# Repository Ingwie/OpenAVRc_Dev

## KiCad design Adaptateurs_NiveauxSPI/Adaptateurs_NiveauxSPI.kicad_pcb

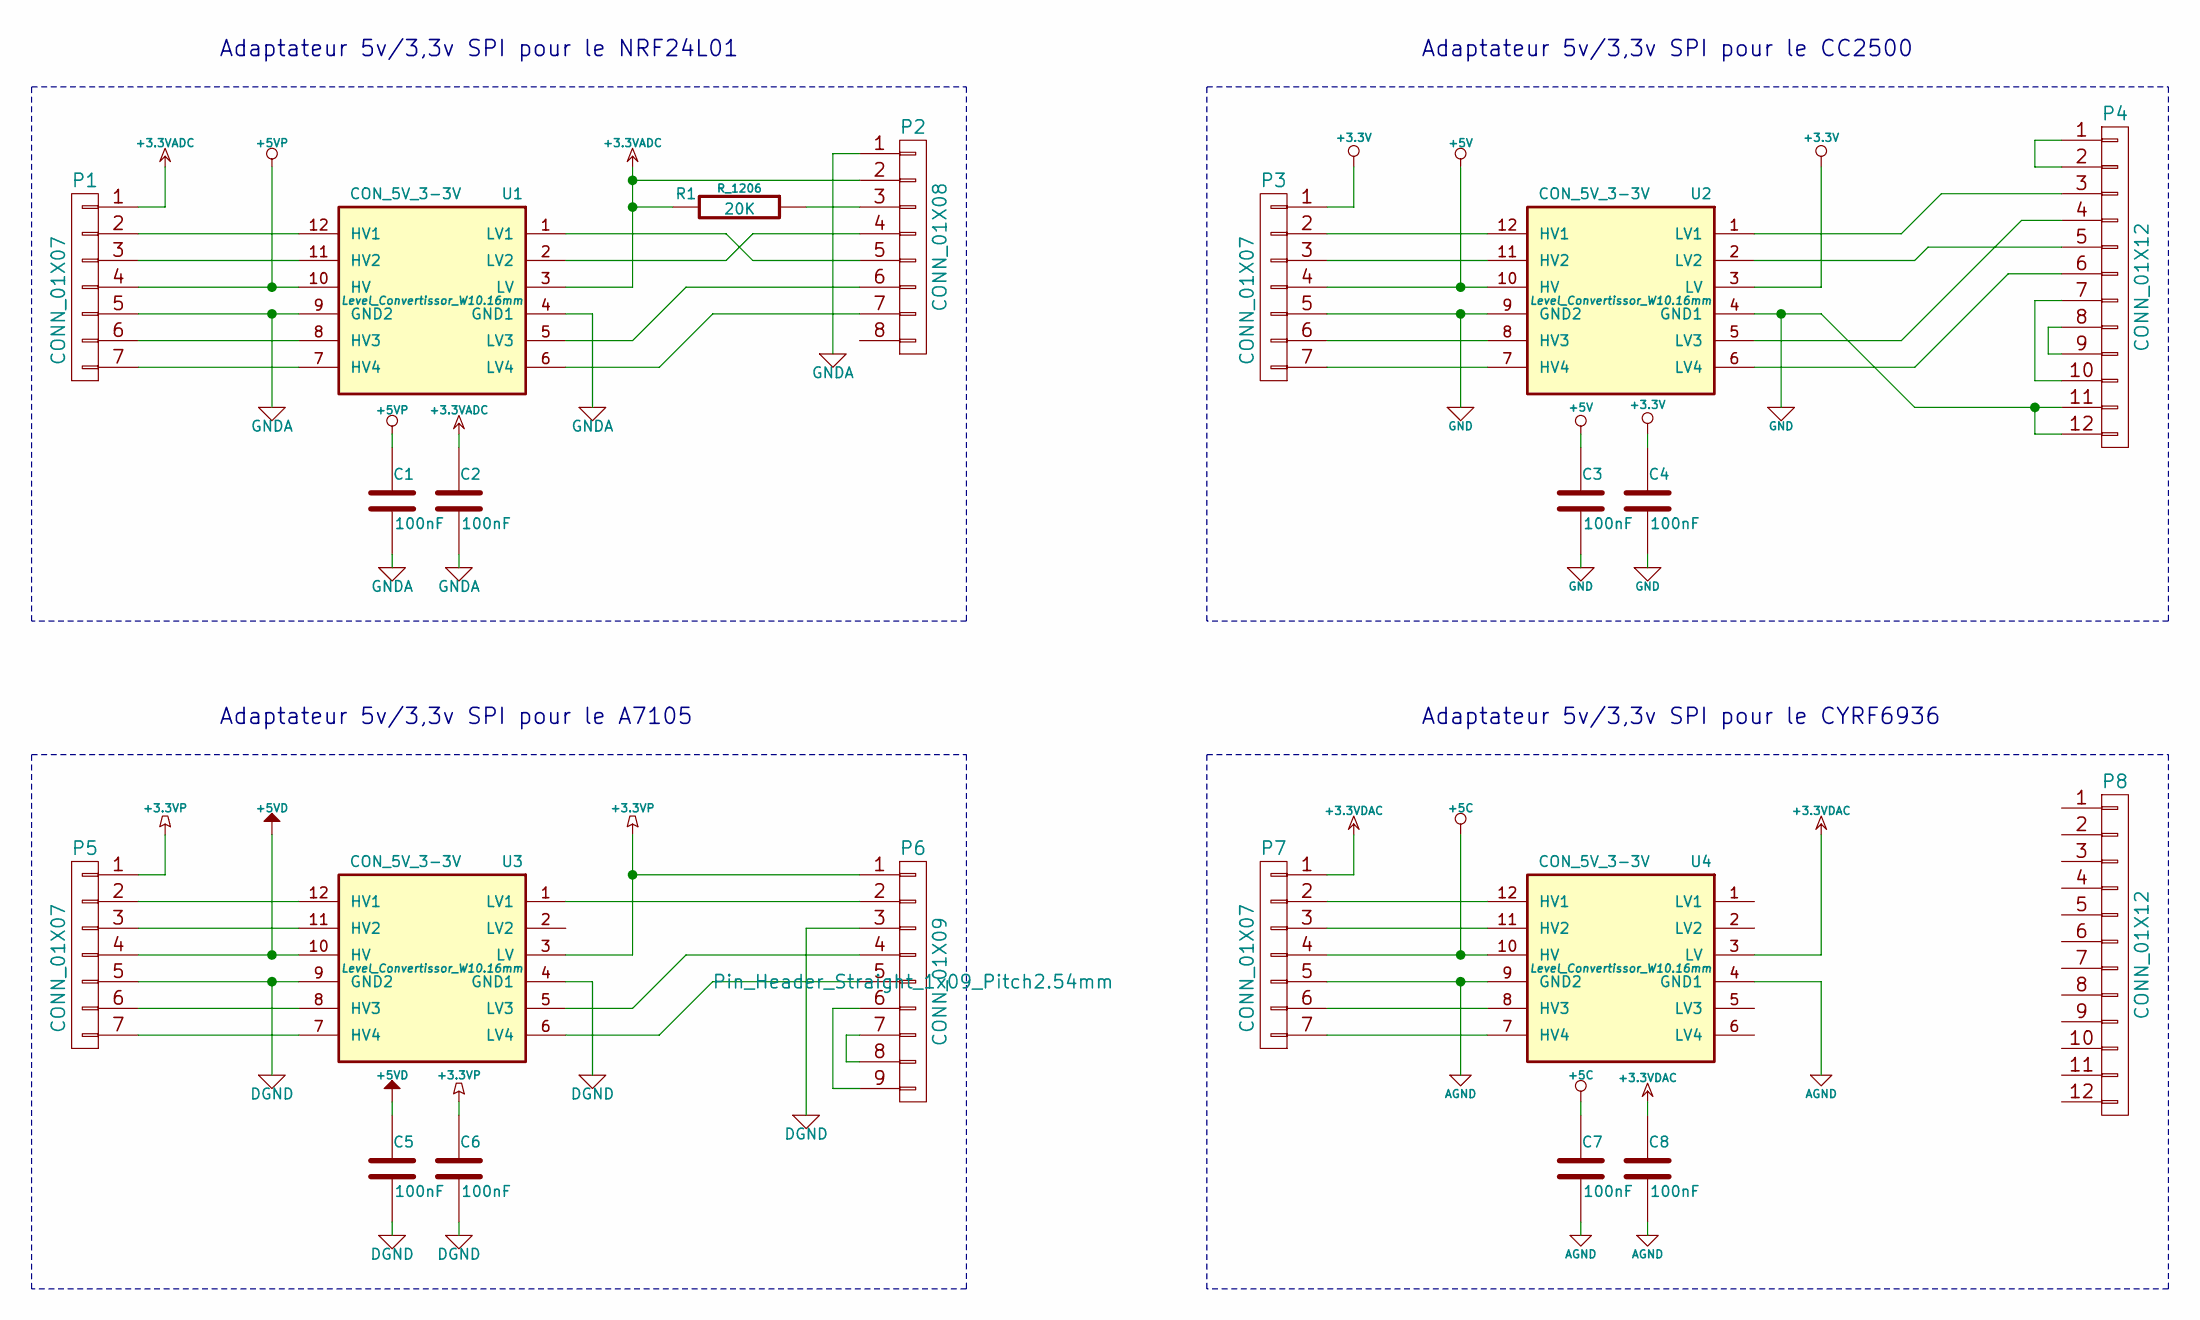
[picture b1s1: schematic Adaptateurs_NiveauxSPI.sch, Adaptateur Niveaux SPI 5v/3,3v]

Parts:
C1, C2, C3, C4, C5, C6, C7, C8: 100nF; C_1206
P1, P3, P5, P7: CONN_01X07; Pin_Header_Straight_1x07_Pitch2.54mm
P2: CONN_01X08; Pin_Header_Straight_2x04_Pitch2.54mm
P4, P8: CONN_01X12; Pin_Header_Straight_2x06_Pitch2.54mm
P6: CONN_01X09; Pin_Header_Straight_1x09_Pitch2.54mm
R1: 20K; R_1206
U1, U2, U3, U4: CON_5V_3-3V; Level_Convertissor_W10.16mm

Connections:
+3.3V: C4.1, P3.1, U2.3 (LV)
+3.3VADC: C2.1, P1.1, P2.2, R1.2, U1.3 (LV)
+3.3VDAC: C8.1, P7.1, U4.3 (LV)
+3.3VP: C6.1, P5.1, P6.1, U3.3 (LV)
+5C: C7.1, P7.4, P8.1, U4.10 (HV)
+5V: C3.1, P3.4, U2.10 (HV)
+5VD: C5.1, P5.4, U3.10 (HV)
+5VP: C1.1, P1.4, U1.10 (HV)
AGND: C7.2, C8.2, P7.5, P8.6, U4.4 (GND1), U4.9 (GND2)
DGND: C5.2, C6.2, P5.5, P6.3, U3.4 (GND1), U3.9 (GND2)
GND: C3.2, C4.2, P3.5, P4.11, P4.12, U2.4 (GND1), U2.9 (GND2)
GNDA: C1.2, C2.2, P1.5, P2.1, U1.4 (GND1), U1.9 (GND2)
unnamed: P1.2, U1.12 (HV1)
unnamed: P1.3, U1.11 (HV2)
unnamed: P1.6, U1.8 (HV3)
unnamed: P1.7, U1.7 (HV4)
unnamed: P2.3, R1.1
unnamed: P2.4, U1.2 (LV2)
unnamed: P2.5, U1.1 (LV1)
unnamed: P2.6, U1.5 (LV3)
unnamed: P2.7, U1.6 (LV4)
unnamed: P3.2, U2.12 (HV1)
unnamed: P3.3, U2.11 (HV2)
unnamed: P3.6, U2.8 (HV3)
unnamed: P3.7, U2.7 (HV4)
unnamed: P4.1, P4.2
unnamed: P4.3, U2.1 (LV1)
unnamed: P4.4, U2.5 (LV3)
unnamed: P4.5, U2.2 (LV2)
unnamed: P4.6, U2.6 (LV4)
unnamed: P4.8, P4.9
unnamed: P4.7, P4.10
unnamed: P5.2, U3.12 (HV1)
unnamed: P5.3, U3.11 (HV2)
unnamed: P5.6, U3.8 (HV3)
unnamed: P5.7, U3.7 (HV4)
unnamed: P6.2, U3.1 (LV1)
unnamed: P6.4, U3.5 (LV3)
unnamed: P6.5, U3.6 (LV4)
unnamed: P6.6, P6.9
unnamed: P6.7, P6.8
unnamed: P7.2, U4.12 (HV1)
unnamed: P7.3, U4.11 (HV2)
unnamed: P7.6, U4.8 (HV3)
unnamed: P7.7, U4.7 (HV4)
unnamed: P8.2, U4.1 (LV1)
unnamed: P8.4, U4.2 (LV2)
unnamed: P8.8, U4.5 (LV3)
unnamed: P8.10, U4.6 (LV4)

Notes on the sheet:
Adaptateur 5v/3,3v SPI pour le NRF24L01
Adaptateur 5v/3,3v SPI pour le CC2500
Adaptateur 5v/3,3v SPI pour le A7105
Adaptateur 5v/3,3v SPI pour le CYRF6936

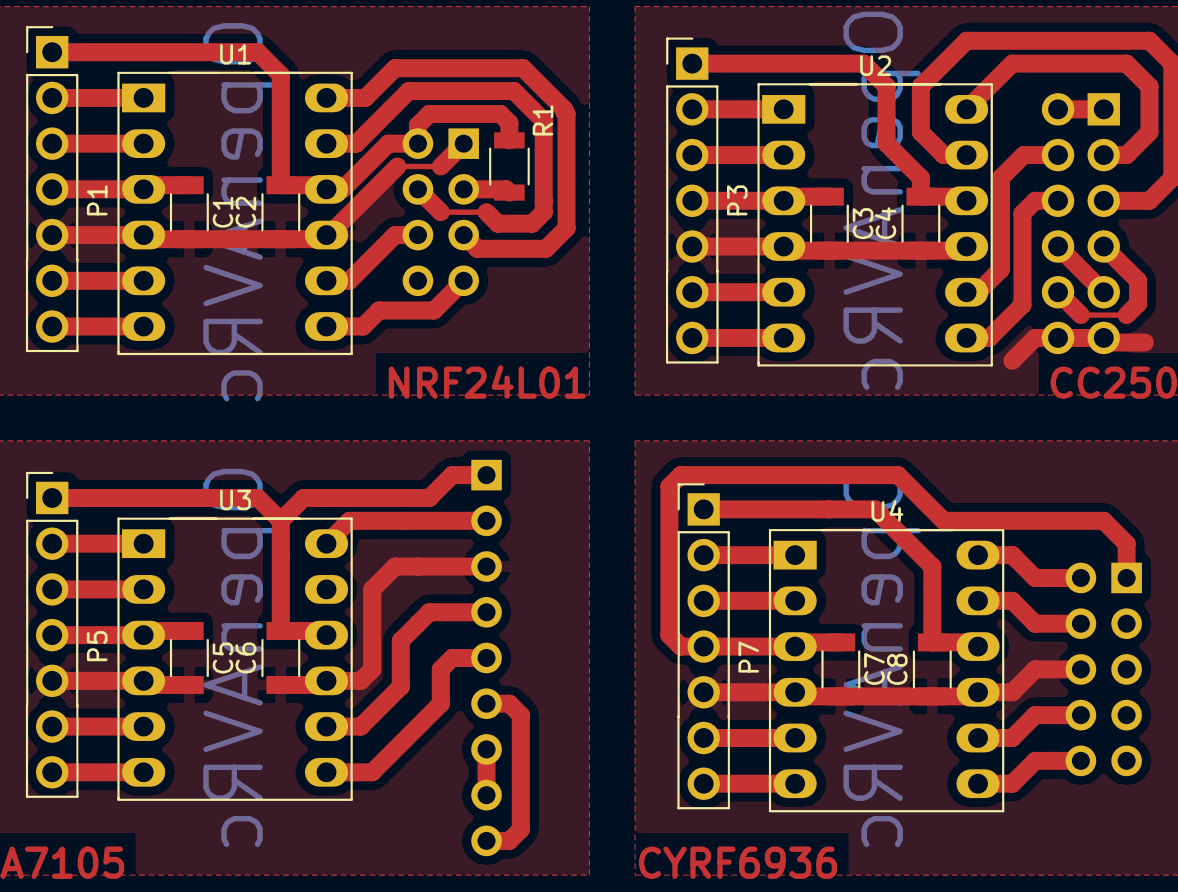
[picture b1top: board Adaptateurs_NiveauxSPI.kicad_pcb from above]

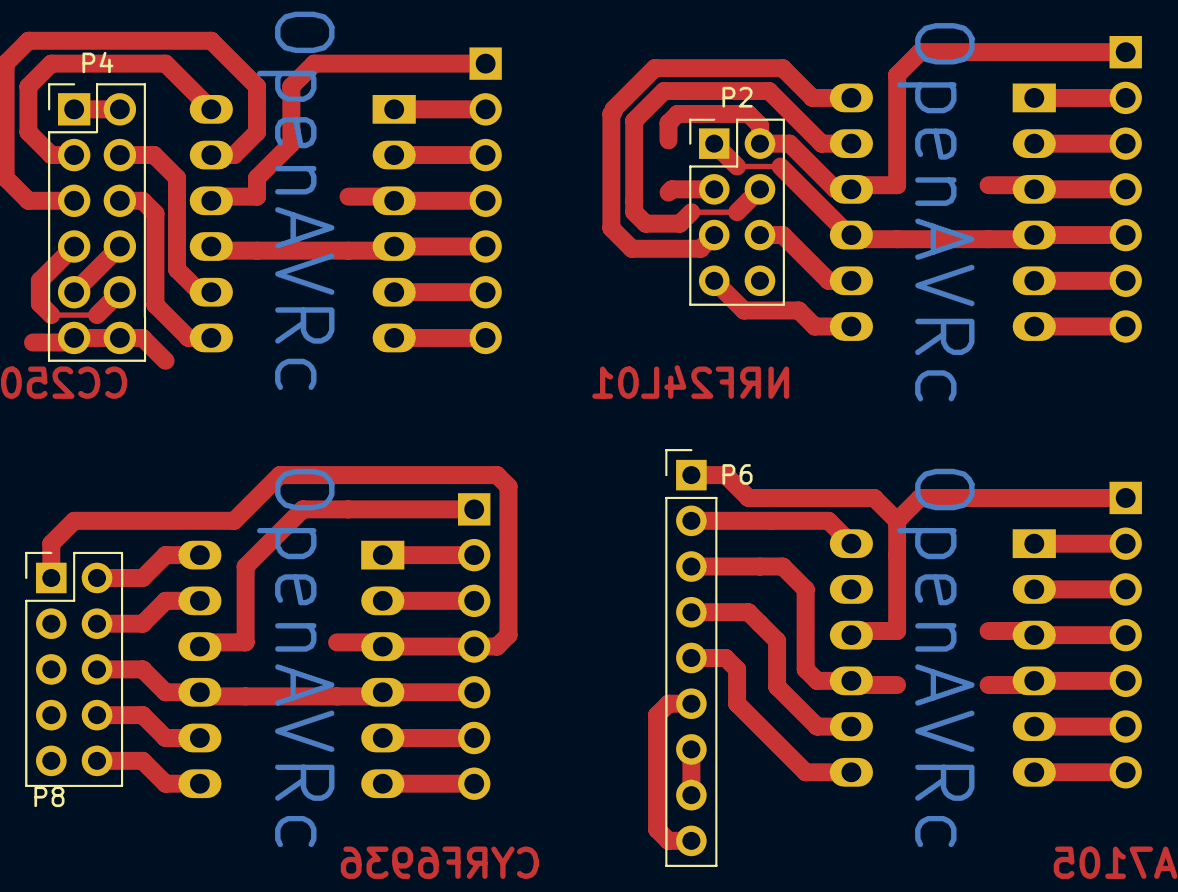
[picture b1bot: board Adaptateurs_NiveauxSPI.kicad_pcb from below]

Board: 2 copper layers, 21 parts (4 on the bottom side), 49 nets.

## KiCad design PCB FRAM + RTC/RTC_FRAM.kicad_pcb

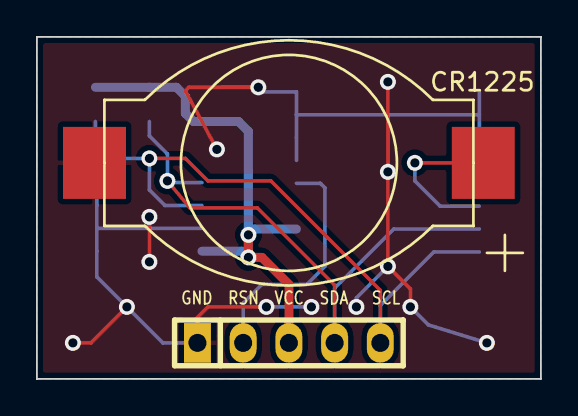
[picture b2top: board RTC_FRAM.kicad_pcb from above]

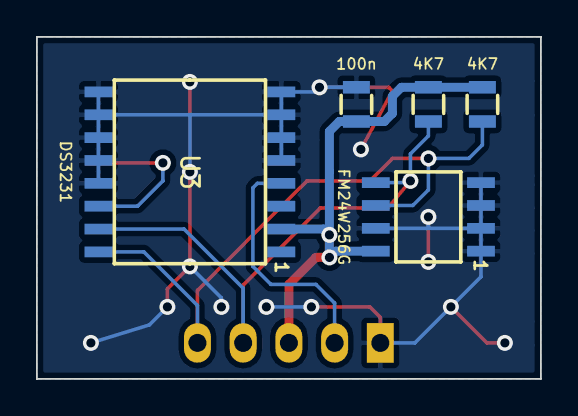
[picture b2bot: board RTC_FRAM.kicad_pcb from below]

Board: 2 copper layers, 28.0 x 19.0 mm, 7 parts (5 on the bottom side), 6 nets.

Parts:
BT1: CR1225; Renata_SMTU1225-LF
C1: 100n; SM0805
J1: CONN_01X05; pin_strip_5
R1, R2: 4K7; SM0805
U2: FM24W256G; SO-8
U3: DS3231; SO-16-W

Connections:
+3V3: C1.1, J1.3, R1.1, R2.1, U2.8, U3.2
GND: BT1.2, C1.2, J1.1, U2.1, U2.2, U2.3, U2.4, U2.7, U3.5, U3.6, U3.7, U3.8, U3.9, U3.10, U3.11, U3.12, U3.13
unnamed: BT1.1, U3.14
RESET_N: J1.2, U3.4
SCL-FRAM-RTC: J1.5, R1.2, U2.6, U3.16
SDA-FRAM-RTC: J1.4, R2.2, U2.5, U3.15

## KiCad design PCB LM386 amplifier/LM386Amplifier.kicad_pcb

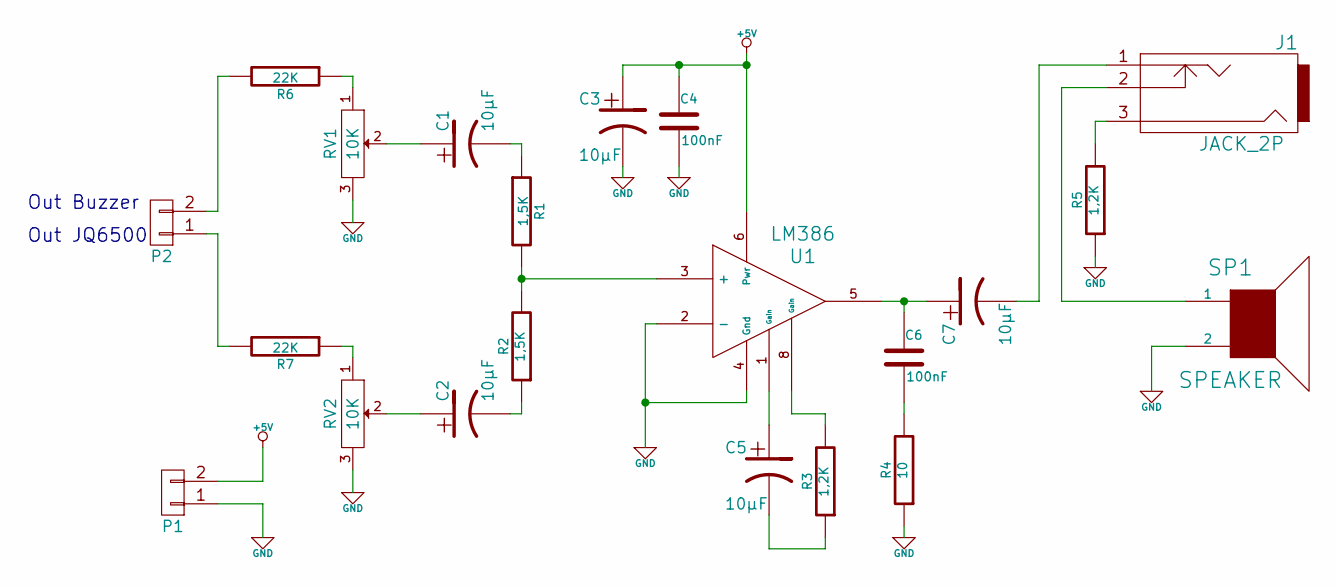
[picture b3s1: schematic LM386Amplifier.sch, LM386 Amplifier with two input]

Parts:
C1, C2, C3: 10µF; CP_Radial_D6.3mm_P2.50mm
C4, C6: 100nF; C_Rect_L7.0mm_W2.0mm_P5.00mm
C5, C7: 10µF; CP_Radial_Tantal_D6.0mm_P2.50mm
J1: JACK_2P; Pin_Header_Straight_1x03_Pitch2.54mm
P1, P2: CONN_01X02; Pin_Header_Straight_1x02_Pitch2.54mm
R1, R2: 1,5K; R_Axial_DIN0204_L3.6mm_D1.6mm_P2.54mm_Vertical
R3, R5: 1,2K; R_Axial_DIN0204_L3.6mm_D1.6mm_P2.54mm_Vertical
R4: 10; R_Axial_DIN0204_L3.6mm_D1.6mm_P2.54mm_Vertical
R6, R7: 22K; R_Axial_DIN0204_L3.6mm_D1.6mm_P2.54mm_Vertical
RV1, RV2: 10K; Potentiometer_Trimmer_Bourns_3296W.kicad_mod
SP1: SPEAKER; Pin_Header_Straight_1x02_Pitch2.54mm
U1: LM386; DIP-8_W7.62mm_LongPads

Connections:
+5V: C3.1, C4.1, P1.2, U1.6 (Pwr)
GND: C3.2, C4.2, P1.1, R4.1, R5.1, RV1.3, RV2.3, SP1.2, U1.2 (-), U1.4 (Gnd)
unnamed: C1.1, RV1.2
unnamed: C1.2, R1.1
unnamed: C2.1, RV2.2
unnamed: C2.2, R2.1
unnamed: C5.1, U1.1 (Gain)
unnamed: C5.2, R3.1
unnamed: C6.1, C7.1, U1.5
unnamed: C6.2, R4.2
unnamed: C7.2, J1.1
unnamed: J1.2, SP1.1
unnamed: J1.3, R5.2
unnamed: P2.1, R7.2
unnamed: P2.2, R6.2
unnamed: R1.2, R2.2, U1.3 (+)
unnamed: R3.2, U1.8 (Gain)
unnamed: R6.1, RV1.1
unnamed: R7.1, RV2.1

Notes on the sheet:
Out Buzzer
Out JQ6500

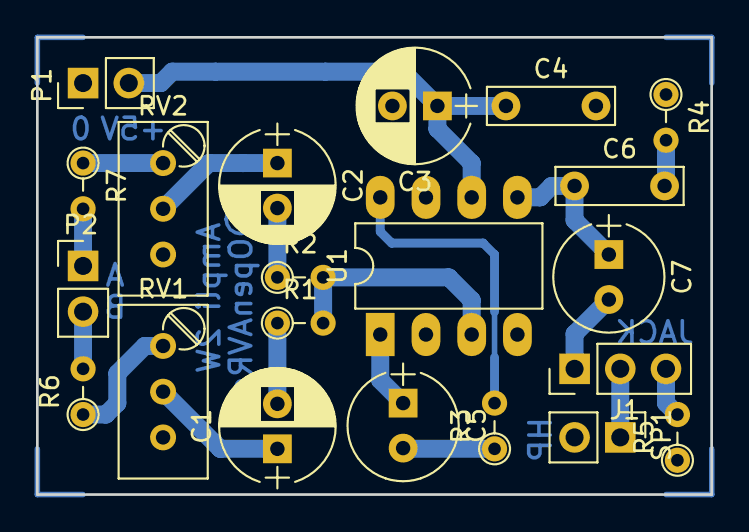
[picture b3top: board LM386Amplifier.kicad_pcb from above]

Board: 2 copper layers, 37.5 x 25.4 mm, 21 parts (0 on the bottom side), 19 nets.

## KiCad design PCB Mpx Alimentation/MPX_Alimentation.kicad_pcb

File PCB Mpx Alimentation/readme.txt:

create PCB Mpx Alimentation directory

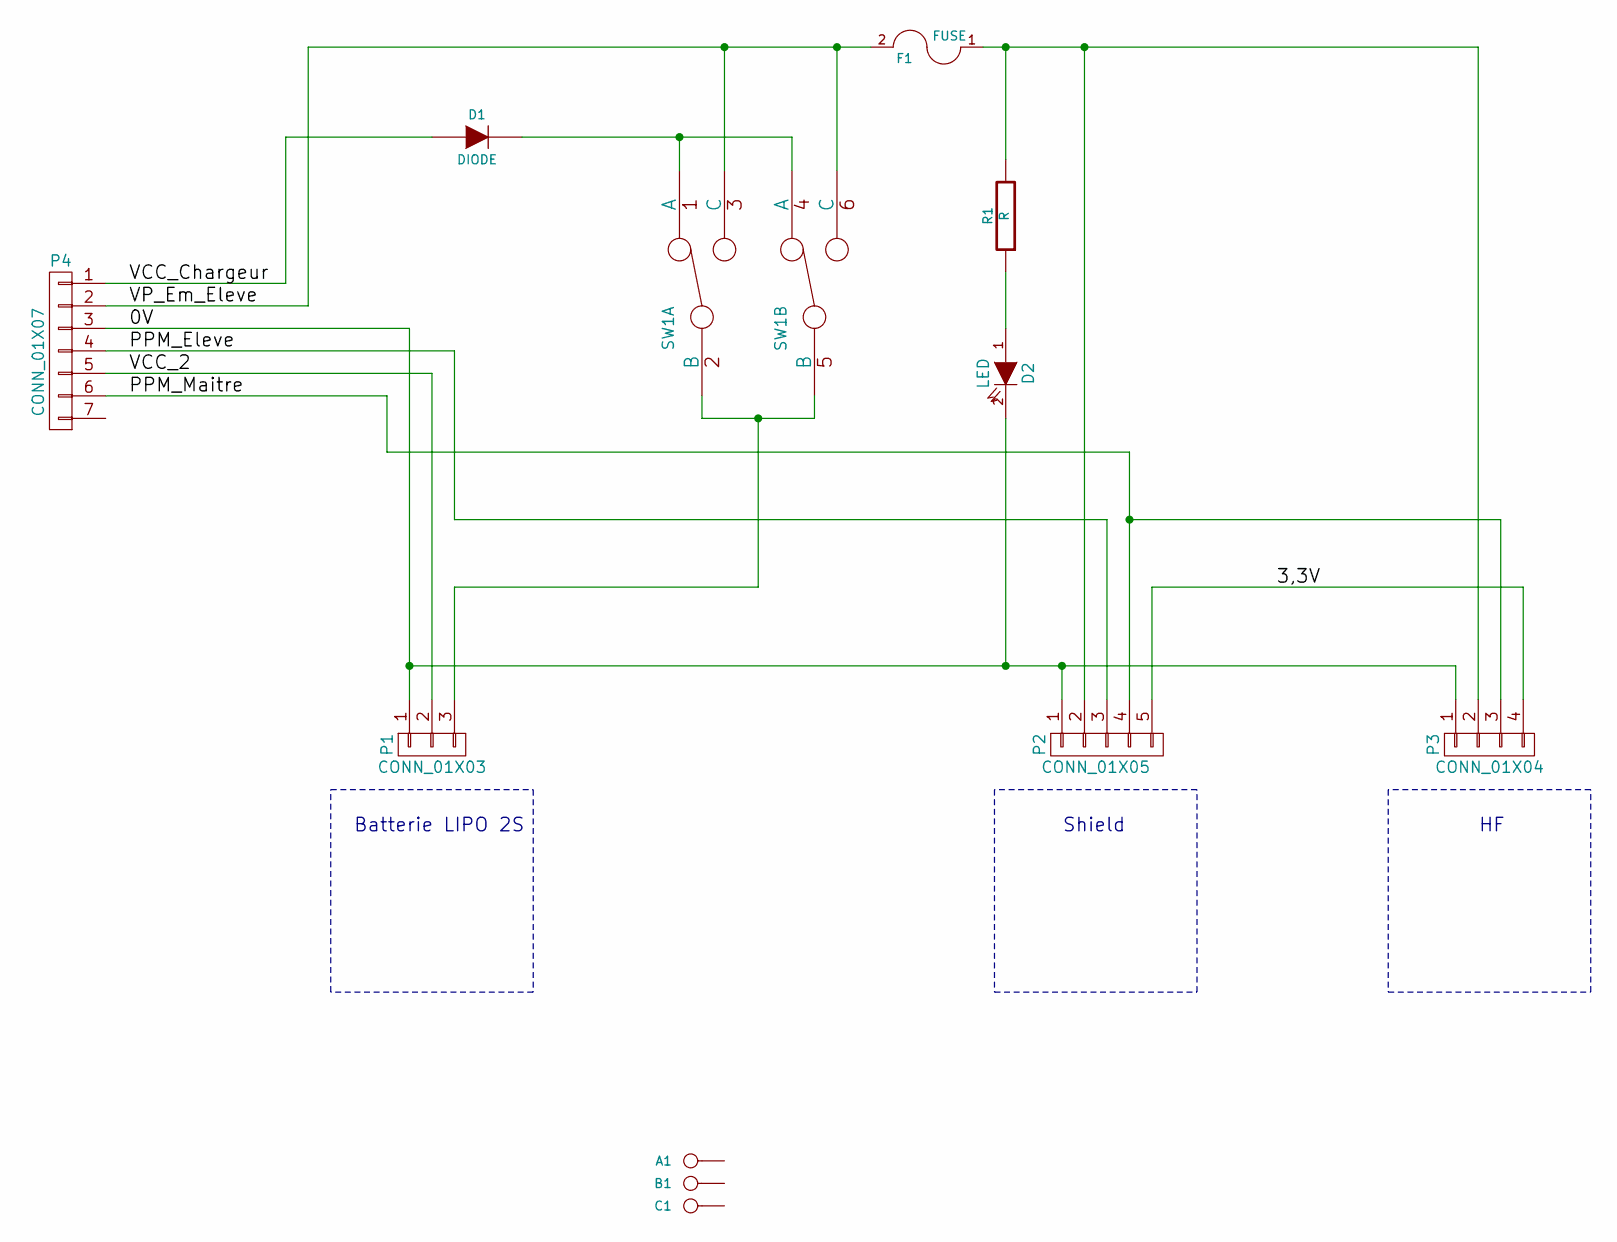
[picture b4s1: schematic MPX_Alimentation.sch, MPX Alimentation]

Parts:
A1: CONN_1; MountingHole_2.2mm_M2
B1: CONN_1; MountingHole_2.2mm_M2
C1: CONN_1; MountingHole_2.2mm_M2
D1: DIODE; D_DO-201_P15.24mm_Horizontal
D2: LED; LED_D3.0mm
F1: FUSE; Fuseholder5x20_horiz_open_universal_Type-III
P1: CONN_01X03; Pin_Header_Angled_1x03_Pitch2.54mm
P2: CONN_01X05; Pin_Header_Angled_1x05_Pitch2.54mm
P3: CONN_01X04; Pin_Header_Angled_1x04_Pitch2.54mm
P4: CONN_01X07; Embase_Din8_Mpx
R1: R; R_Axial_DIN0207_L6.3mm_D2.5mm_P10.16mm_Horizontal
SW1: DUAL_SWITCH_INV; SW_CuK_JS202011CQN_DPDT_Straight

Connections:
/0V: D2.2 (K), P1.1, P2.1, P3.1, P4.3
/3,3V: P2.5, P3.4
/PPM_Eleve: P2.3, P4.4
/PPM_Maitre: P2.4, P3.3, P4.6
/VCC_2: P1.2, P4.5
/VCC_Chargeur: D1.1 (A), P4.1
/VP_Em_Eleve: F1.2, P4.2, SW1.3 (C), SW1.6 (C)
unnamed: D1.2 (K), SW1.1 (A), SW1.4 (A)
unnamed: D2.1 (A), R1.1
unnamed: F1.1, P2.2, P3.2, R1.2
unnamed: P1.3, SW1.2 (B), SW1.5 (B)

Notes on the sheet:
Batterie LIPO 2S
Shield

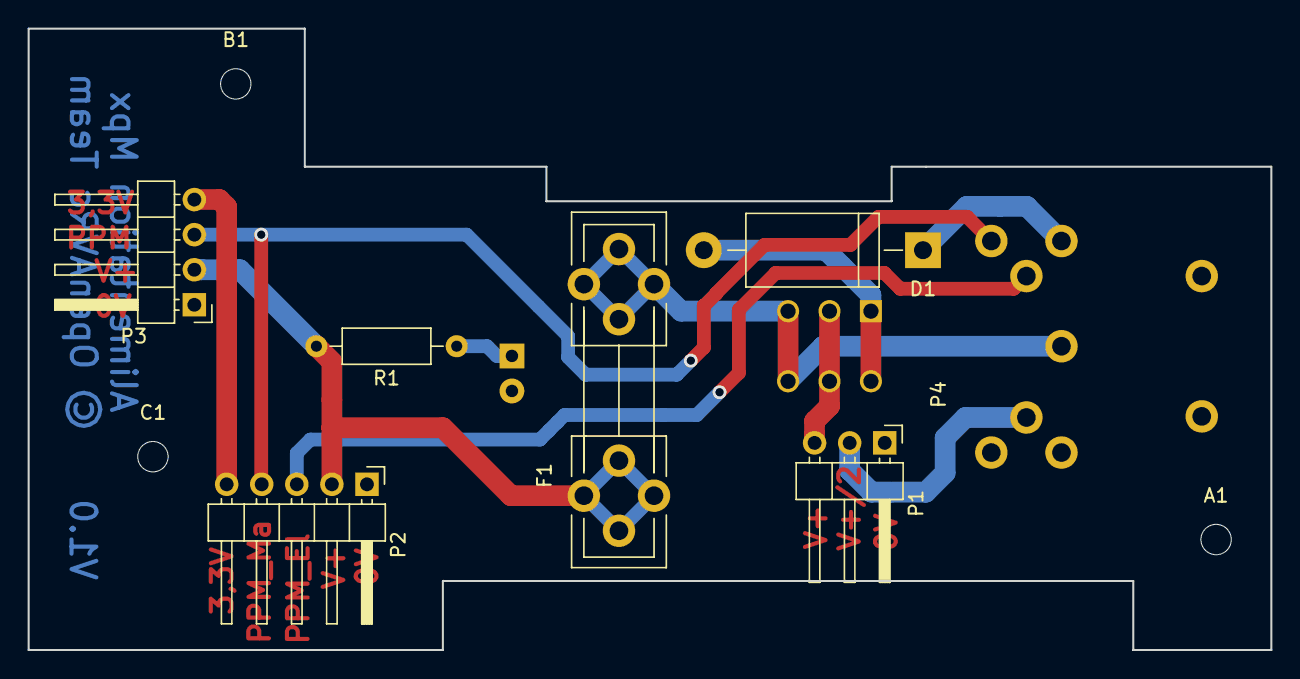
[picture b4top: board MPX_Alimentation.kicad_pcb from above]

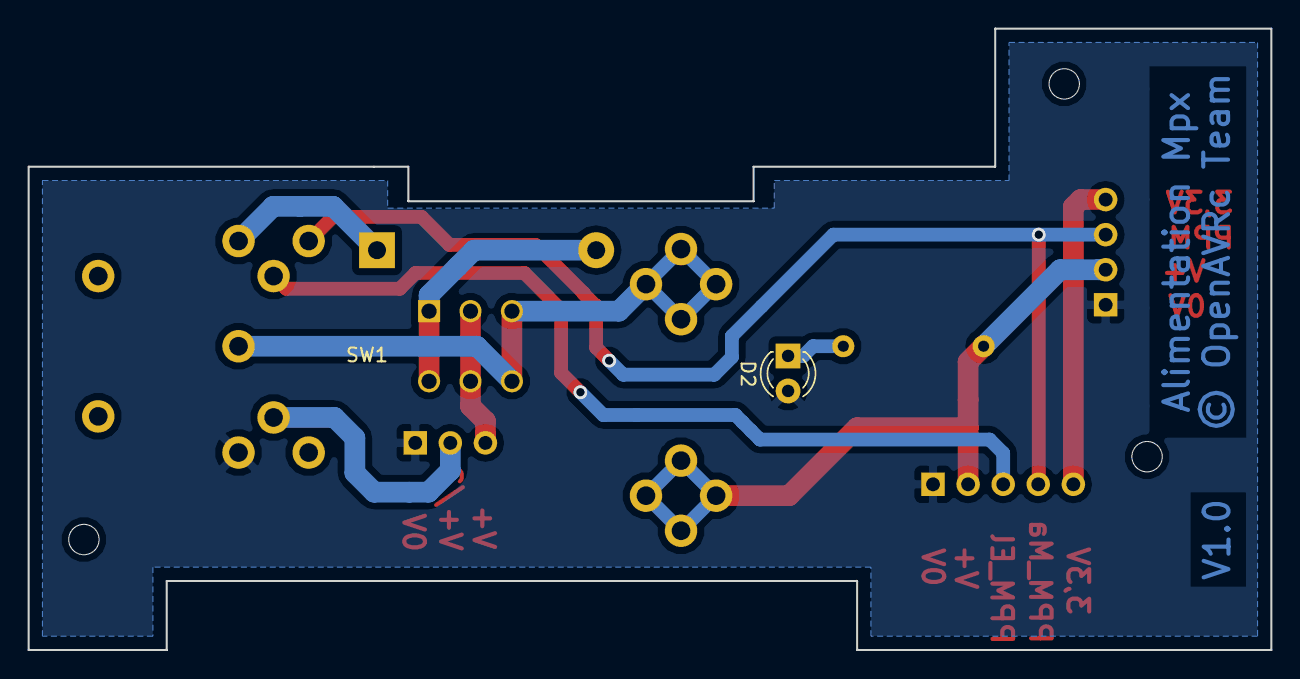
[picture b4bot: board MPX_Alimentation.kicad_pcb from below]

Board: 2 copper layers, 90.0 x 45.0 mm, 12 parts (2 on the bottom side), 11 nets.

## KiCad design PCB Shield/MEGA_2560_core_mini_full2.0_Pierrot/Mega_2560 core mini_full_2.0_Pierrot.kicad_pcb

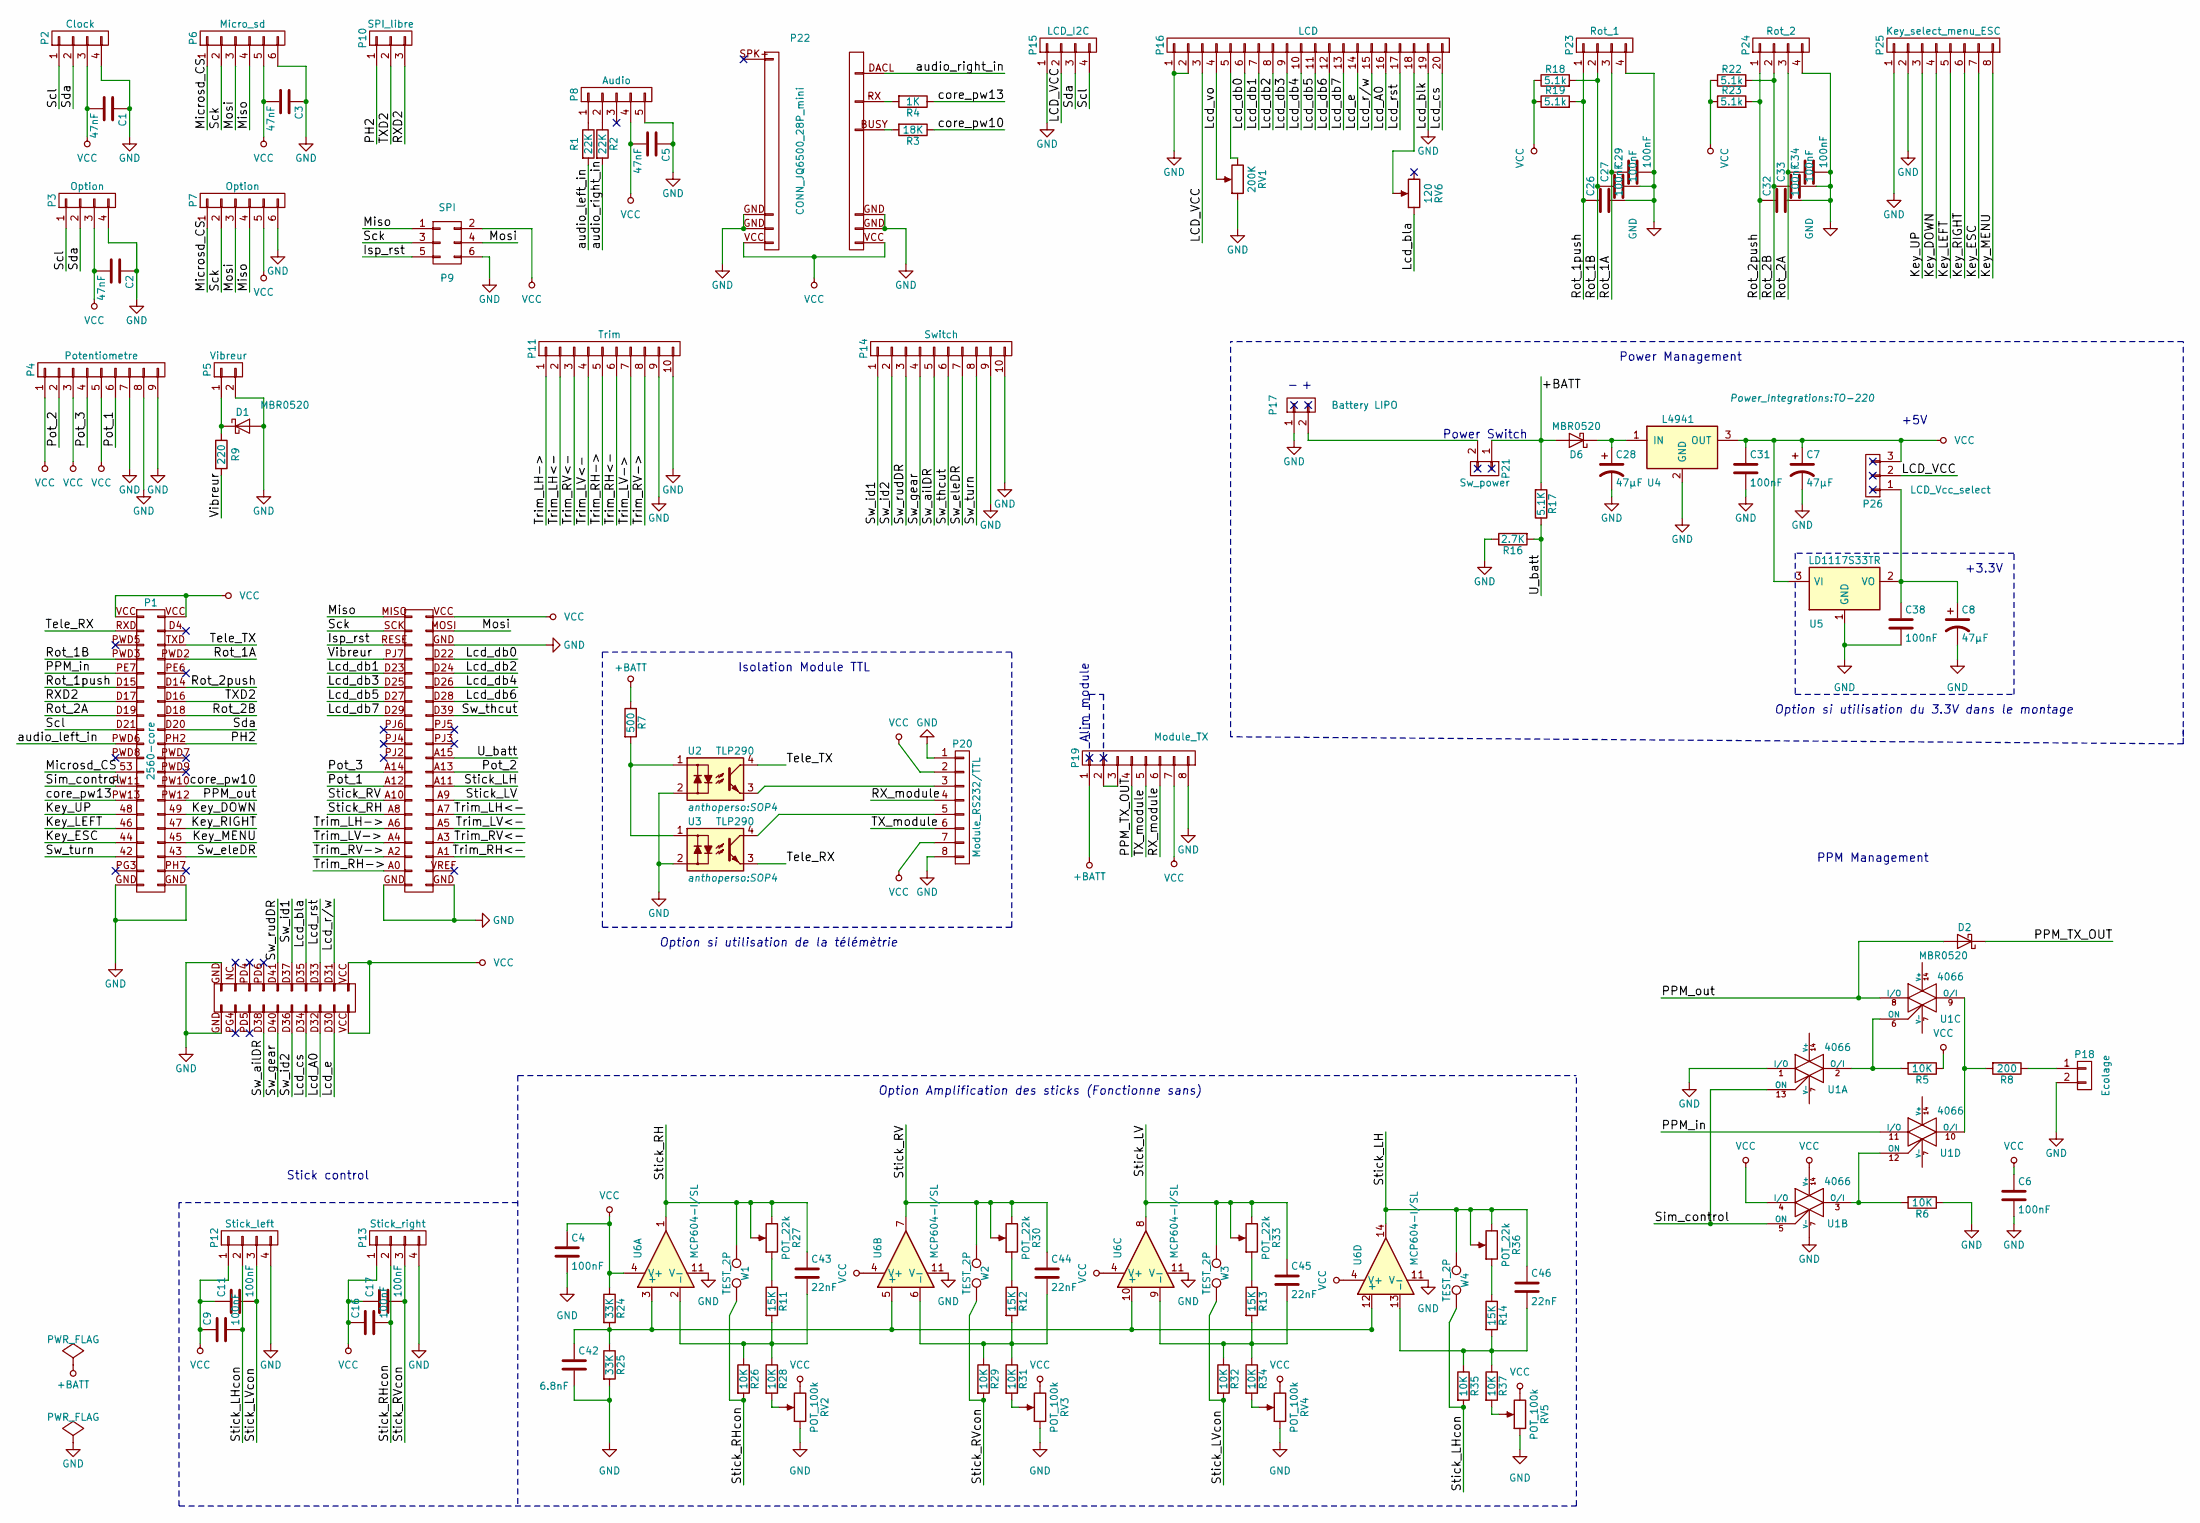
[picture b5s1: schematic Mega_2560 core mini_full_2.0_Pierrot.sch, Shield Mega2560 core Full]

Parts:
C1, C2, C3, C5: 47nF; C_1206
C4, C6, C9, C11, C16, C17, C26, C27, C29, C31, C32, C33, C34, C38: 100nF; C_1206
C7, C8, C28: 47µF; CP_Elec_6.3x5.3
C42: 6.8nF; C_1206
C43, C44, C45, C46: 22nF; C_1206
D1, D2, D6: MBR0520; D_SOD-123
P1: 2560-core; Connectors-2560-core
P2: Clock; Pin_Header_Straight_1x04_Pitch2.54mm
P3: Option; Pin_Header_Straight_1x04_Pitch2.54mm
P4: Potentiometre; Pin_Header_Straight_2x05_Pitch2.54mm
P5: Vibreur; Pin_Header_Straight_1x02_Pitch2.54mm
P6: Micro_sd; Pin_Header_Straight_1x06_Pitch2.54mm
P7: Option; Pin_Header_Straight_1x06_Pitch2.54mm
P8: Audio; Pin_Header_Straight_1x05_Pitch2.54mm
P9: SPI; Pin_Header_Straight_2x03_Pitch2.54mm
P10: SPI_libre; Pin_Header_Straight_1x03_Pitch2.54mm
P11: Trim; Pin_Header_Straight_2x05_Pitch2.54mm
P12: Stick_left; Pin_Header_Straight_1x04_Pitch2.54mm
P13: Stick_right; Pin_Header_Straight_1x04_Pitch2.54mm
P14: Switch; Pin_Header_Straight_2x05_Pitch2.54mm
P15: LCD_I2C; Pin_Header_Straight_1x04_Pitch2.54mm
P16: LCD; Pin_Header_Straight_2x10_Pitch2.54mm
P17: Battery LIPO; Pin_Header_Straight_1x02_Pitch2.54mm
P18: Ecolage; Pin_Header_Straight_1x02_Pitch2.54mm
P19: Module_TX; Pin_Header_Straight_2x04_Pitch2.54mm
P20: Module_RS232/TTL; Con_RS232_TTL
P21: Sw_power; Pin_Header_Straight_1x02_Pitch2.54mm
P22: CONN_JQ6500_28P_mini; connector_mini-JQ6500-28P
P23: Rot_1; Pin_Header_Straight_1x04_Pitch2.54mm
P24: Rot_2; Pin_Header_Straight_1x04_Pitch2.54mm
P25: Key_select_menu_ESC; Pin_Header_Straight_2x04_Pitch2.54mm
P26: LCD_Vcc_select; Pin_Header_Straight_1x03_Pitch2.54mm
R1, R2: 22K; R_1206
R3: 18K; R_1206
R4: 1K; R_1206
R5, R6, R26, R28, R29, R31, R32, R34, R35, R37: 10K; R_1206
R7: 500; R_1206
R8: 200; R_1206
R9: 220; R_1206
R11, R12, R13, R14: 15K; R_1206
R16: 2.7K; R_1206
R17: 5.1K; R_1206
R18, R19, R22, R23: 5.1k; R_1206
R24, R25: 33K; R_1206
R27, R30, R33, R36: POT_22k; Potentiometer_Trimmer_Bourns_3296W
RV1: 200K; Potentiometer_Triwood_RM-065
RV2, RV3, RV4, RV5: POT_100k; Potentiometer_Bourns_3296W_3-8Zoll_Inline_ScrewUp
RV6: 120; Potentiometer_Trimmer_Bourns_3266W
U1: 4066; SOP14
U2, U3: TLP290; SOP4
U4: L4941; TO-220
U5: LD1117S33TR; SOT-223
U6: MCP604-I/SL; SOP14
W1, W2, W3, W4: TEST_2P; TESTPT

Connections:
+BATT: D6.2 (A), P19.1, P21.1, R7.1, R17.2
/Isp_rst: P1.RESE (P75), P9.5
/Key_DOWN: P1.49 (P29), P25.4
/Key_ESC: P1.44 (P34), P25.7
/Key_LEFT: P1.46 (P32), P25.5
/Key_MENU: P1.45 (P33), P25.8
/Key_RIGHT: P1.47 (P31), P25.6
/Key_UP: P1.48 (P30), P25.3
/LCD_VCC: P15.2, P16.3, P26.2
/Lcd_A0: P1.D32 (P85), P16.16
/Lcd_bla: P1.D35 (P88), RV6.1
/Lcd_cs: P1.D34 (P87), P16.20
/Lcd_db0: P1.D22 (P74), P16.6
/Lcd_db1: P1.D23 (P71), P16.7
/Lcd_db2: P1.D24 (P72), P16.8
/Lcd_db3: P1.D25 (P69), P16.9
/Lcd_db4: P1.D26 (P70), P16.10
/Lcd_db5: P1.D27 (P67), P16.11
/Lcd_db6: P1.D28 (P68), P16.12
/Lcd_db7: P1.D29 (P65), P16.13
/Lcd_e: P1.D30 (P83), P16.14
/Lcd_r/w: P1.D31 (P84), P16.15
/Lcd_rst: P1.D33 (P86), P16.17
/Lcd_vo: P16.4, RV1.2
/Microsd_CS: P1.53 (P24), P6.1, P7.1
/Miso: P1.MISO (P79), P6.4, P7.4, P9.1
/Mosi: P1.MOSI (P78), P6.3, P7.3, P9.4
/PH2: P1.PH2 (P19), P10.1
/PPM_TX_OUT: D2.1 (K), P19.4
/PPM_in: P1.PE7 (P10), U1.11 (I/O)
/PPM_out: D2.2 (A), P1.PW12 (P27), U1.8 (I/O)
/Pot_1: P1.A12 (P55), P4.6
/Pot_2: P1.A13 (P58), P4.2
/Pot_3: P1.A14 (P57), P4.4
/RXD2: P1.D17 (P14), P10.3
/RX_module: P19.6, P20.4
/Rot_1A: C29.1, P1.PWD2 (P7), P23.3
/Rot_1B: C27.1, P1.PWD3 (P8), P23.2, R18.2
/Rot_1push: C26.1, P1.D15 (P12), P23.1, R19.2
/Rot_2A: C34.1, P1.D19 (P16), P24.3
/Rot_2B: C33.1, P1.D18 (P15), P24.2, R22.2
/Rot_2push: C32.1, P1.D14 (P11), P24.1, R23.2
/Sck: P1.SCK (P77), P6.2, P7.2, P9.3
/Scl: P1.D21 (P18), P2.1, P3.1, P15.4
/Sda: P1.D20 (P17), P2.2, P3.2, P15.3
/Sim_control: P1.PW11 (P26), U1.5 (ON), U1.13 (ON)
/Stick_LH: C46.1, P1.A11 (P56), R36.2, R36.3, U6.14, W4.1
/Stick_LHcon: C9.2, P12.2, R35.2, W4.2
/Stick_LV: C45.1, P1.A9 (P54), R33.2, R33.3, U6.8, W3.1
/Stick_LVcon: C11.2, P12.3, R32.2, W3.2
/Stick_RH: C43.1, P1.A8 (P51), R27.2, R27.3, U6.1, W1.1
/Stick_RHcon: C16.2, P13.2, R26.2, W1.2
/Stick_RV: C44.1, P1.A10 (P53), R30.2, R30.3, U6.7, W2.1
/Stick_RVcon: C17.2, P13.3, R29.2, W2.2
/Sw_ailDR: P1.D38 (P93), P14.5
/Sw_eleDR: P1.43 (P35), P14.7
/Sw_gear: P1.D40 (P91), P14.4
/Sw_id1: P1.D37 (P90), P14.1
/Sw_id2: P1.D36 (P89), P14.2
/Sw_rudDR: P1.D41 (P92), P14.3
/Sw_thcut: P1.D39 (P66), P14.6
/Sw_turn: P1.42 (P36), P14.8
/TXD2: P1.D16 (P13), P10.2
/TX_module: P19.5, P20.6
/Tele_RX: P1.RXD (P4), U3.3
/Tele_TX: P1.TXD (P5), U2.4
/Trim_LH->: P1.A6 (P49), P11.1
/Trim_LH<-: P1.A7 (P52), P11.2
/Trim_LV->: P1.A4 (P47), P11.7
/Trim_LV<-: P1.A5 (P50), P11.4
/Trim_RH->: P1.A0 (P43), P11.5
/Trim_RH<-: P1.A1 (P46), P11.6
/Trim_RV->: P1.A2 (P45), P11.8
/Trim_RV<-: P1.A3 (P48), P11.3
/U_batt: P1.A15 (P60), R16.2, R17.1
/Vibreur: P1.PJ7 (P73), R9.2
/audio_left_in: P1.PWD6 (P20), R1.2
/audio_right_in: P22.DACL (P16), R2.2
/core_pw10: P1.PW10 (P25), R3.1
/core_pw13: P1.PW13 (P28), R4.1
GND: C1.1, C2.1, C3.1, C4.2, C5.1, C6.2, C7.2, C8.2, C26.2, C27.2, C28.2, C29.2, C31.2, C32.2, C33.2, C34.2, C38.2, C42.2, D1.2 (A), P1.GND (P100), P2.4, P3.4, P4.7, P4.8, P4.9, P5.2, P6.6, P7.6, P8.5, P9.6, P11.9, P11.10, P12.4, P13.4, P14.9, P14.10, P15.1, P16.1, P16.2, P16.19, P17.1, P18.2, P19.8, P20.1, P20.8, P22.GND (P12), P23.4, P24.4, P25.1, P25.2, R6.1, R16.1, R25.2, RV1.1, RV2.1, RV3.1, RV4.1, RV5.1, U1.1 (I/O), U1.7 (V-), U2.2, U3.2, U4.2 (GND), U5.1 (GND), U6.11 (V-)
unnamed: C28.1, D6.1 (K), U4.1 (IN)
unnamed: C8.1, C38.1, P26.1, U5.2 (VO)
unnamed: C42.1, R24.2, R25.1, U6.3 (+), U6.5 (+), U6.10 (+), U6.12 (+)
unnamed: C43.2, R11.2, R26.1, R28.1, U6.2 (-)
unnamed: C44.2, R12.2, R29.1, R31.1, U6.6 (-)
unnamed: C45.2, R13.2, R32.1, R34.1, U6.9 (-)
unnamed: C46.2, R14.2, R35.1, R37.1, U6.13 (-)
unnamed: D1.1 (K), P5.1, R9.1
unnamed: P8.1, R1.1
unnamed: P8.2, R2.1
unnamed: P16.5, RV1.3
unnamed: P16.18, RV6.2
unnamed: P17.2, P21.2
unnamed: P18.1, R8.1
unnamed: P19.2, P19.3
unnamed: P20.3, U2.3
unnamed: P20.5, U3.4
unnamed: P22.BUSY (P20), R3.2
unnamed: P22.RX (P18), R4.2
unnamed: R5.2, U1.2 (O/I), U1.6 (ON)
unnamed: R6.2, U1.3 (O/I), U1.12 (ON)
unnamed: R7.2, U2.1, U3.1
unnamed: R8.2, U1.9 (O/I), U1.10 (O/I)
unnamed: R11.1, R27.1
unnamed: R12.1, R30.1
unnamed: R13.1, R33.1
unnamed: R14.1, R36.1
unnamed: R28.2, RV2.2
unnamed: R31.2, RV3.2
unnamed: R34.2, RV4.2
unnamed: R37.2, RV5.2
VCC: C1.2, C2.2, C3.2, C4.1, C5.2, C6.1, C7.1, C9.1, C11.1, C16.1, C17.1, C31.1, P1.VCC (P1), P2.3, P3.3, P4.1, P4.3, P4.5, P6.5, P7.5, P8.4, P9.2, P12.1, P13.1, P19.7, P20.2, P20.7, P22.VCC (P14), P26.3, R5.1, R18.1, R19.1, R22.1, R23.1, R24.1, RV2.3, RV3.3, RV4.3, RV5.3, U1.4 (I/O), U1.14 (V+), U4.3 (OUT), U5.3 (VI), U6.4 (V+)

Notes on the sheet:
+3.3V
+5V
Isolation Module TTL
Power Management
PPM Management
Stick control
Option si utilisation du 3.3V dans le montage
Option Amplification des sticks (Fonctionne sans)
Option si utilisation de la télémètrie
Alim module
Power Switch

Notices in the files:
PCB FRAM + RTC/RTC_FRAM.kicad_pcb:
Copyright © 2017 R Kilvington (eclrpk @ leeds.ac.uk)
PCB LM386 amplifier/LM386Amplifier.kicad_pcb:
©OpenAVRc
PCB Mpx Alimentation/MPX_Alimentation.kicad_pcb:
© OpenAVRc Team
PCB Shield/Mega_2560 core mini_full_2.0_PM/OpenAVRc_Audio_Haptic.sch:
© Team OpenAVRc
